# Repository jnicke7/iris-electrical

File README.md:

# iris-electrical

IRIS Electrical Team Arduino Code Repository

## void setup()

First code run by Arduino on start

Sets up serial inputs for the sabertooth from the Odroid

Assigns the direct and pwm pins as outputs to the LACs

## void loop()

Runs after setup

Creates the checksum to make sure that the data is being passed through to the Arduino correctly

Uses largestOneIndex helper function to calculate

CRC: Cyclic Redundancy Check

If the checksum came out incorrect then it will ignore the instruction.

### Motor ID Values:

    0: Left Drive
    1: Right Drive
    2: Bucket Ladder M
    3: Dump Conveyor LA
    4: Bucket Ladder LA
    5: Agitator
    6: Dump Conveyor M
    7: Shuts off all motors

Based on the motor ID value it will call the sabertooth or the linear actuators

## void linac(int power, int motor)

Inputs: power number and the specific motor number

Outputs: direction and power specific to a motor

Creates changes with two functions:

### digitalWrite(dir\_1, (int)(OdroidIn[1]/128));

Sets the direction of a given motor

### analogWrite(pwm\_3, power\*2);

Sets the magnitude of the given motor

## void stop()

This function runs through each motor and reduces its speed to 0

## int largestOneIndex(unsignedint curr)

This function parses through curr bitwise to find the index of the most significant '1'

Inputs: curr, 16-bit chars

Outputs: integer i, the first index of '1'

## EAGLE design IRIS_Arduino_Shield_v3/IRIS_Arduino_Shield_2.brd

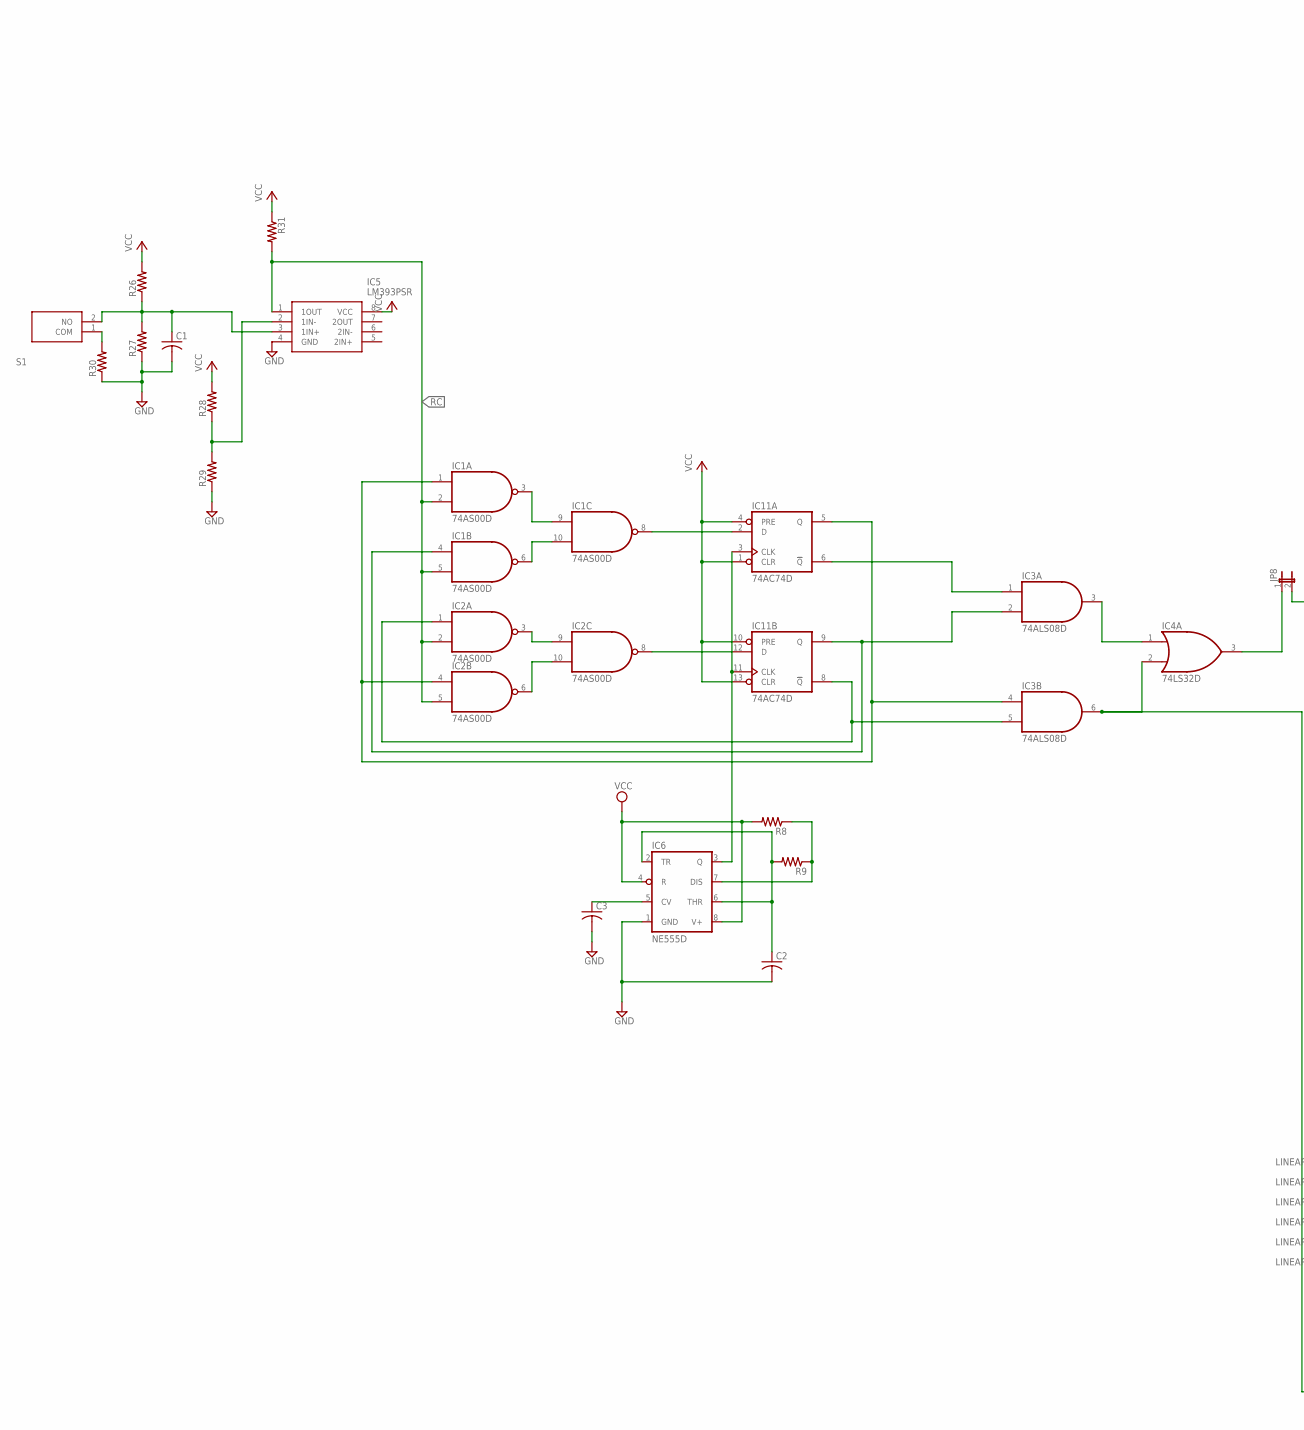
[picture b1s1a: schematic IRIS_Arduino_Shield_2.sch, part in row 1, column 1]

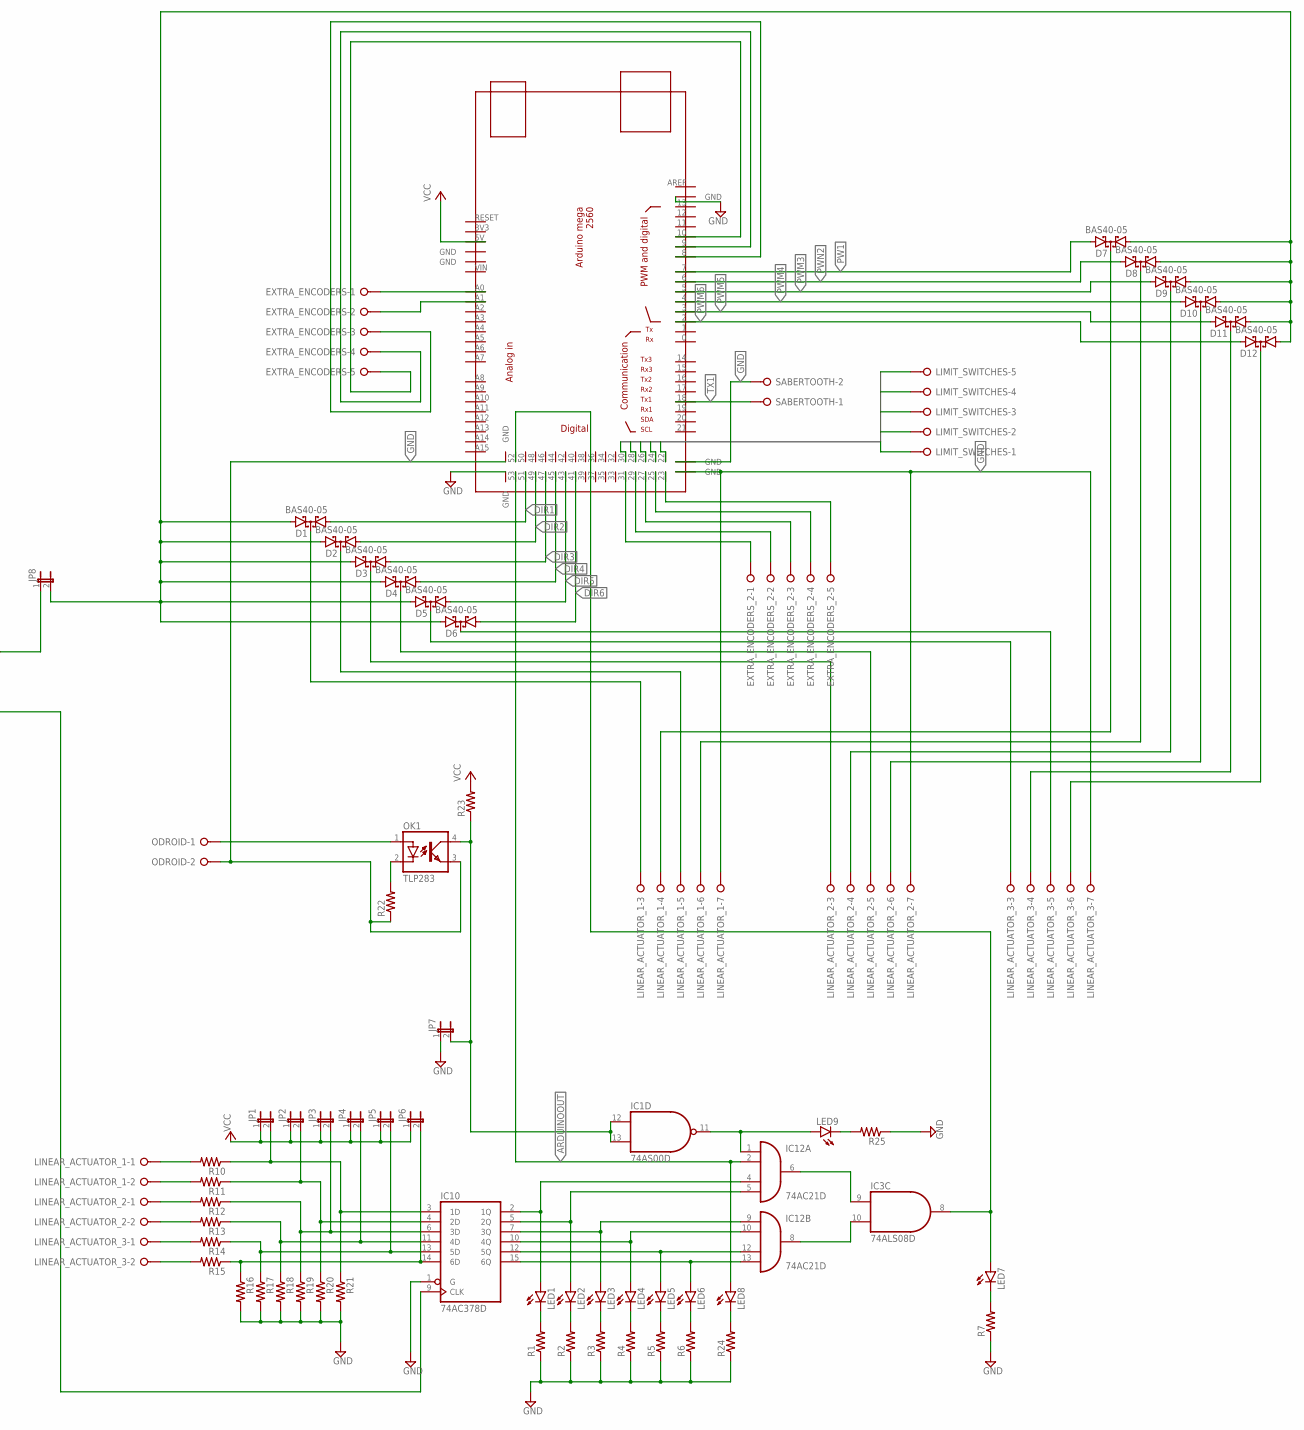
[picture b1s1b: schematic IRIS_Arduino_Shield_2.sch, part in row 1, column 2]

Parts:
C1, C2, C3: C-USC0805; C0805
D1, D2, D3, D4, D5, D6, D7, D8, D9, D10, D11, D12: BAS40-05; SOT23
EXTRA_ENCODERS: W237-05P; W237-5P
EXTRA_ENCODERS_2: W237-05P; W237-5P
IC1, IC2: 74AS00D; SO14
IC3: 74ALS08D; SO14
IC4: 74LS32D; SO14
IC5: LM393PSR; SOIC127P780X200-8N
IC6: NE555D; SO08
IC10: 74AC378D; SO16
IC11: 74AC74D; SO14
IC12: 74AC21D; SO14
JP1, JP2, JP3, JP4, JP5, JP6, JP7, JP8: JP1E; JP1
LED1, LED2, LED3, LED4, LED5, LED6, LED7, LED8, LED9: LEDCHIPLED_1206; CHIPLED_1206
LIMIT_SWITCHES: W237-05P; W237-5P
LINEAR_ACTUATOR_1, LINEAR_ACTUATOR_2, LINEAR_ACTUATOR_3: W237-07P; W237-7P
ODROID: W237-02P; W237-132
OK1: TLP283; MINI-FLAT-4
R1, R2, R3, R4, R5, R6, R7, R8, R9, R10, R11, R12, R13, R14, R15, R16, R17, R18, R19, R20, R21, R22, R23, R24, R25, R26, R27, R28, R29, R30, R31: R-US_R0805; R0805
S1: PTS636_SL43_SMTR_LFS; PTS636SL43SMTRLFS
SABERTOOTH: W237-02P; W237-132
U$1: MEGA_DEVICE; MEGAOUTLINE

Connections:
ARDUINOOUT: IC12.2 (I1), LED8.A, U$1.53
DIR1: D1.1 (A1), U$1.51
DIR2: D2.1 (A1), U$1.49
DIR3: D3.1 (A1), U$1.47
DIR4: D4.1 (A1), U$1.45
DIR5: D5.1 (A1), U$1.43
DIR6: D6.1 (A1), U$1.41
GND: C1.2, C2.2, C3.2, IC1.7 (GND), IC2.7 (GND), IC3.7 (GND), IC4.7 (GND), IC5.4 (GND), IC6.1 (GND), IC10.1 (G), IC10.8 (GND), IC11.7 (GND), IC12.7 (GND), JP7.1, LINEAR_ACTUATOR_1.7, LINEAR_ACTUATOR_2.7, LINEAR_ACTUATOR_3.7, ODROID.2, OK1.3 (EMIT), R1.1, R2.1, R3.1, R4.1, R5.1, R6.1, R7.1, R16.2, R17.2, R18.2, R19.2, R20.2, R21.2, R22.1, R24.1, R25.1, R27.1, R29.1, R30.1, SABERTOOTH.2, U$1.GND@1 (GND), U$1.GND@4 (GND), U$1.GND@5 (GND), U$1.GND@6 (GND), U$1.GND@7 (GND)
LA_TEST: D1.2 (A2), D2.2 (A2), D3.2 (A2), D4.2 (A2), D5.2 (A2), D6.2 (A2), D7.1 (A1), D8.1 (A1), D9.1 (A1), D10.1 (A1), D11.1 (A1), D12.1 (A1), JP8.2
unnamed: IC1.3 (O), IC1.9 (I0)
unnamed: IC1.6 (O), IC1.10 (I1)
unnamed: IC1.8 (O), IC11.2 (D)
unnamed: D7.3 (C), LINEAR_ACTUATOR_1.4
unnamed: IC6.3 (Q), IC11.3 (CLK), IC11.11 (CLK)
unnamed: IC2.8 (O), IC11.12 (D)
unnamed: LED1.C, R1.2
unnamed: LED2.C, R2.2
unnamed: LED3.C, R3.2
unnamed: LED4.C, R4.2
unnamed: LED5.C, R5.2
unnamed: LED6.C, R6.2
unnamed: IC10.2 (1Q), IC12.4 (I2), LED1.A
unnamed: IC10.5 (2Q), IC12.5 (I3), LED2.A
unnamed: IC10.7 (3Q), IC12.9 (I0), LED3.A
unnamed: IC10.10 (4Q), IC12.10 (I1), LED4.A
unnamed: IC10.12 (5Q), IC12.12 (I2), LED5.A
unnamed: IC10.15 (6Q), IC12.13 (I3), LED6.A
unnamed: IC3.9 (I0), IC12.6 (O)
unnamed: IC3.10 (I1), IC12.8 (O)
unnamed: IC3.8 (O), LED7.A, U$1.52
unnamed: LED7.C, R7.2
unnamed: IC2.3 (O), IC2.9 (I0)
unnamed: IC2.6 (O), IC2.10 (I1)
unnamed: IC4.3 (O), JP8.1
unnamed: C1.1, IC5.3 (1IN+), R26.1, R27.2, S1.2 (NO)
unnamed: IC5.2 (1IN-), R28.1, R29.2
unnamed: C2.1, IC6.2 (TR), IC6.6 (THR), R9.2
unnamed: D1.3 (C), LINEAR_ACTUATOR_1.3
unnamed: IC6.7 (DIS), R8.1, R9.1
unnamed: IC3.1 (I0), IC11.6 (!Q)
unnamed: IC10.3 (1D), JP1.2, R10.1, R21.1
unnamed: ODROID.1, OK1.1 (A)
unnamed: IC10.4 (2D), JP2.2, R11.1, R20.1
unnamed: IC10.6 (3D), JP3.2, R12.1, R19.1
unnamed: IC10.11 (4D), JP4.2, R13.1, R18.1
unnamed: IC10.13 (5D), JP5.2, R14.1, R17.1
unnamed: IC10.14 (6D), JP6.2, R15.1, R16.1
unnamed: D8.3 (C), LINEAR_ACTUATOR_1.6
unnamed: D9.3 (C), LINEAR_ACTUATOR_2.4
unnamed: IC2.1 (I0), IC3.5 (I1), IC11.8 (!Q)
unnamed: IC1.1 (I0), IC2.4 (I0), IC3.4 (I0), IC11.5 (Q)
unnamed: IC1.4 (I0), IC3.2 (I1), IC11.9 (Q)
unnamed: D10.3 (C), LINEAR_ACTUATOR_2.6
unnamed: D11.3 (C), LINEAR_ACTUATOR_3.4
unnamed: LED8.C, R24.2
unnamed: OK1.2 (C), R22.2
unnamed: LED9.C, R25.2
unnamed: IC1.12 (I0), IC1.13 (I1), JP7.2, OK1.4 (COL), R23.1
unnamed: EXTRA_ENCODERS.1, U$1.A0
unnamed: IC1.11 (O), IC12.1 (I0), LED9.A
unnamed: EXTRA_ENCODERS.2, U$1.A1
unnamed: EXTRA_ENCODERS.4, U$1.9
unnamed: R30.2, S1.1 (COM)
unnamed: D2.3 (C), LINEAR_ACTUATOR_1.5
unnamed: EXTRA_ENCODERS.3, U$1.8
unnamed: D3.3 (C), LINEAR_ACTUATOR_2.3
unnamed: D4.3 (C), LINEAR_ACTUATOR_2.5
unnamed: D5.3 (C), LINEAR_ACTUATOR_3.3
unnamed: D6.3 (C), LINEAR_ACTUATOR_3.5
unnamed: D12.3 (C), LINEAR_ACTUATOR_3.6
unnamed: IC3.6 (O), IC4.2 (I1), IC10.9 (CLK)
unnamed: LINEAR_ACTUATOR_1.1, R10.2
unnamed: LINEAR_ACTUATOR_1.2, R11.2
unnamed: LINEAR_ACTUATOR_2.1, R12.2
unnamed: LINEAR_ACTUATOR_2.2, R13.2
unnamed: LINEAR_ACTUATOR_3.1, R14.2
unnamed: LINEAR_ACTUATOR_3.2, R15.2
unnamed: C3.1, IC6.5 (CV)
unnamed: EXTRA_ENCODERS.5, U$1.10
unnamed: IC3.3 (O), IC4.1 (I0)
unnamed: EXTRA_ENCODERS_2.5, U$1.23
unnamed: EXTRA_ENCODERS_2.4, U$1.25
unnamed: EXTRA_ENCODERS_2.3, U$1.27
unnamed: EXTRA_ENCODERS_2.2, U$1.29
unnamed: EXTRA_ENCODERS_2.1, U$1.31
unnamed: LIMIT_SWITCHES.1, U$1.30
unnamed: LIMIT_SWITCHES.2, U$1.28
unnamed: LIMIT_SWITCHES.3, U$1.26
unnamed: LIMIT_SWITCHES.4, U$1.24
unnamed: LIMIT_SWITCHES.5, U$1.22
PW1: D7.2 (A2), U$1.7
PWM3: D9.2 (A2), U$1.5
PWM4: D10.2 (A2), U$1.4
PWM5: D11.2 (A2), U$1.3
PWM6: D12.2 (A2), U$1.2
PWN2: D8.2 (A2), U$1.6
RC: IC1.2 (I1), IC1.5 (I1), IC2.2 (I1), IC2.5 (I1), IC5.1 (1OUT), R31.2
TX1: SABERTOOTH.1, U$1.18
VCC: IC1.14 (VCC), IC2.14 (VCC), IC3.14 (VCC), IC4.14 (VCC), IC5.8 (VCC), IC6.4 (R), IC6.8 (V+), IC10.16 (VCC), IC11.1 (CLR), IC11.4 (PRE), IC11.10 (PRE), IC11.13 (CLR), IC11.14 (VCC), IC12.14 (VCC), JP1.1, JP2.1, JP3.1, JP4.1, JP5.1, JP6.1, R8.2, R23.2, R26.2, R28.2, R31.1, U$1.5V

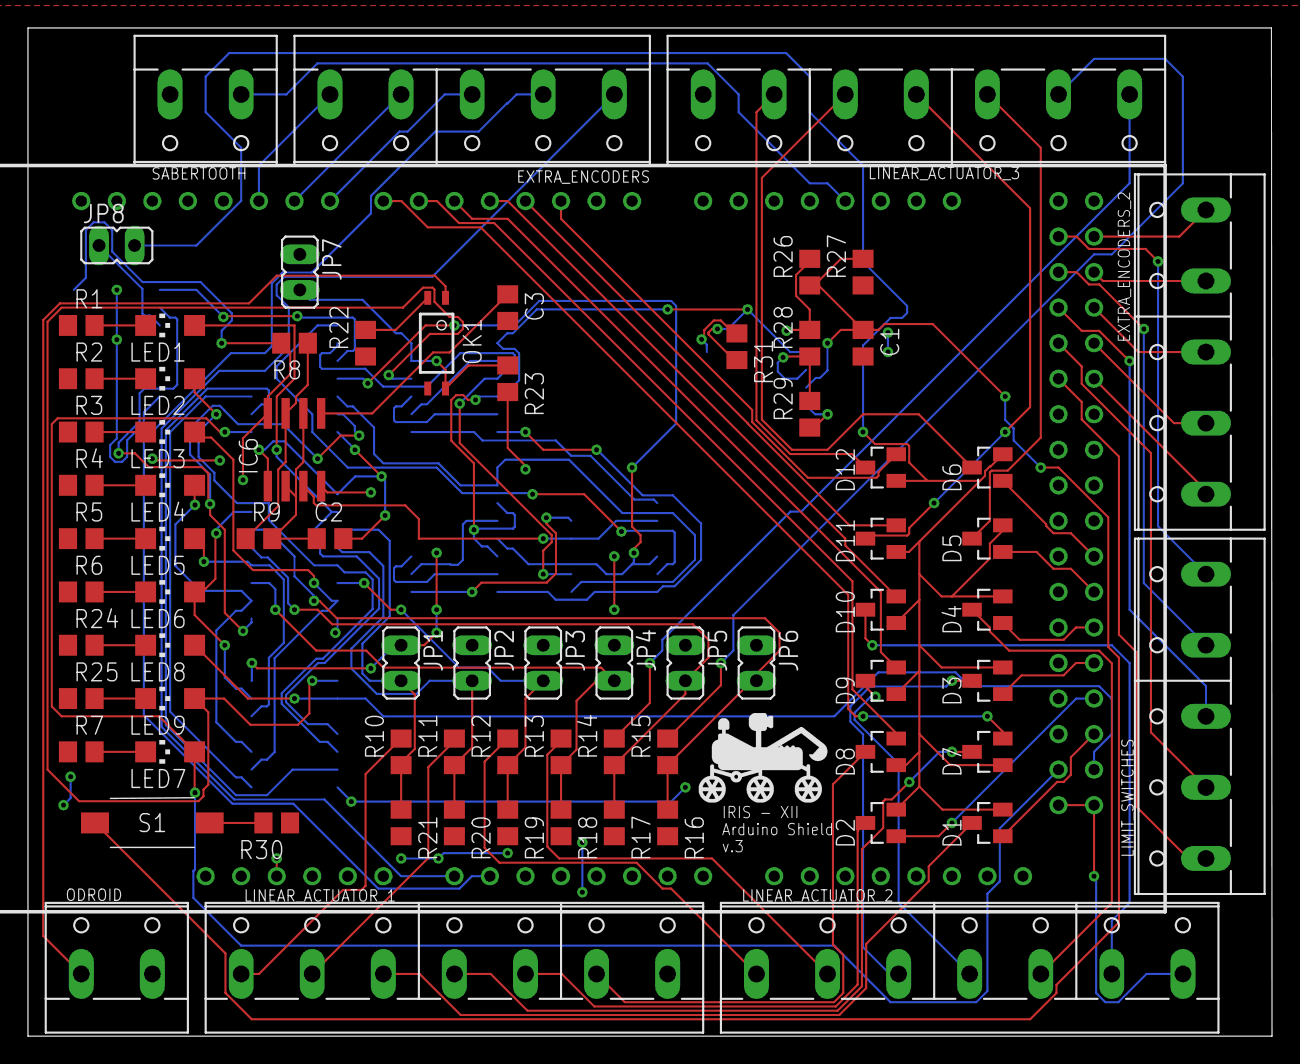
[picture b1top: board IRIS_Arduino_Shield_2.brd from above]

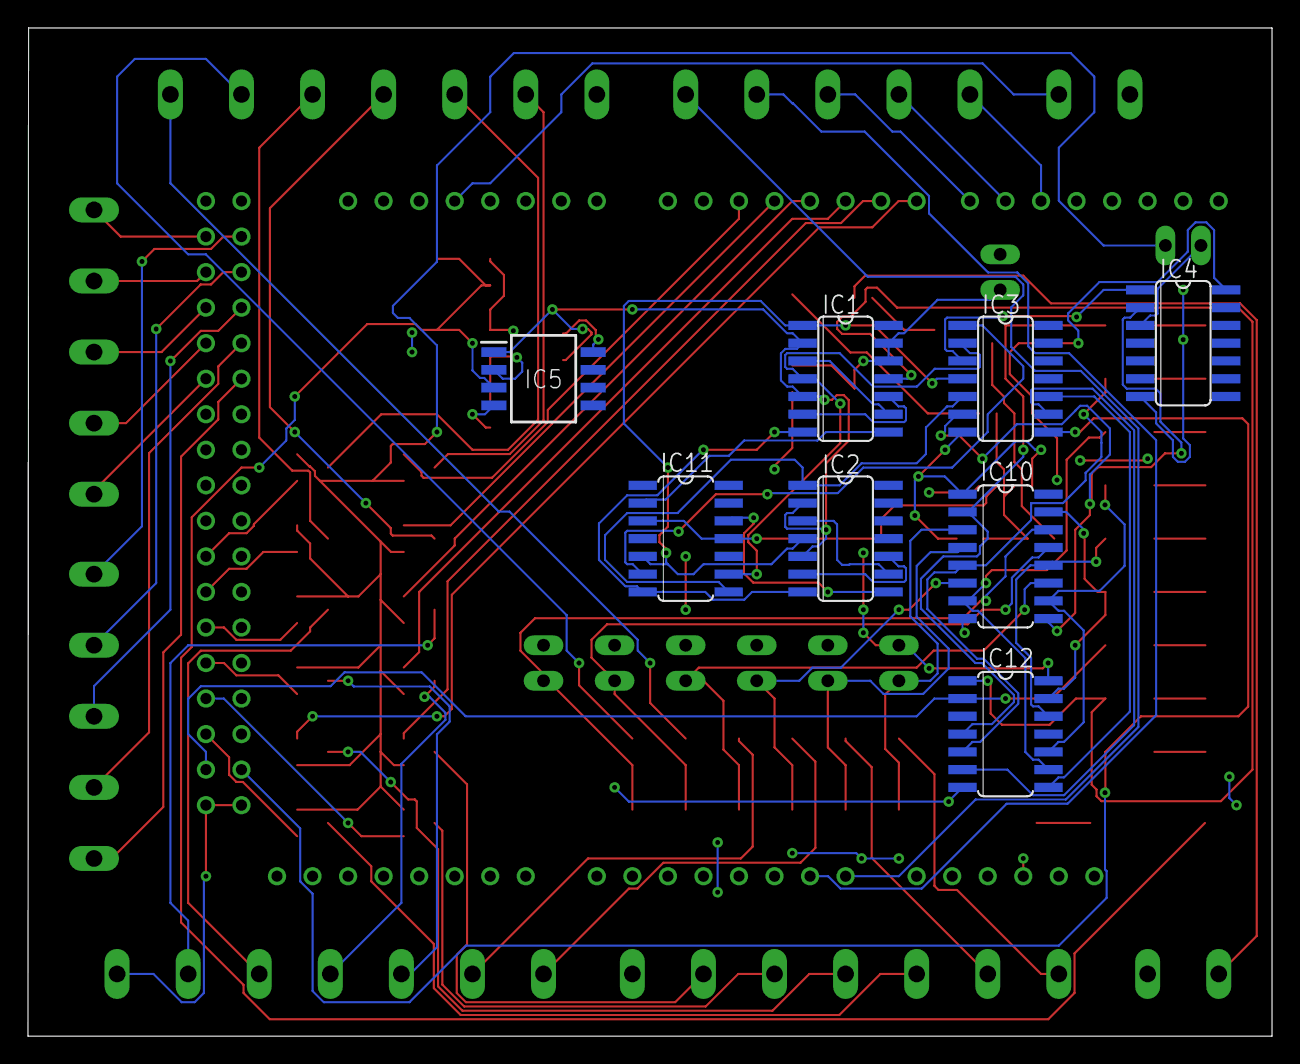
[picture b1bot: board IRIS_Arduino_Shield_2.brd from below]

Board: 2 copper layers, 88.9 x 72.1 mm, 83 parts (8 on the bottom side), 99 nets.

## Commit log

2020-10-07 Added motorcontrol.ino
2020-10-08 10/7
    Added arduino code for Sabertooth/linAC, and added sabertooth library
2020-10-09 added serial input basic
2020-10-09 10/8 Serial input and CRC
2020-10-15 Pushing motor control loop changes
2020-10-15 Algorithm checking and rework for bytewise input
2020-10-16 Pushign template python code for writeMotor
2020-10-22 Updated readme file with documentation
2020-10-30 Added EAGLE files
2020-11-05 Removed zone identifier files
2020-11-05 Removed more unnecessary files
2021-11-03 Added board v3
